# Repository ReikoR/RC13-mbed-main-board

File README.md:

RC13-mbed-main-board
====================

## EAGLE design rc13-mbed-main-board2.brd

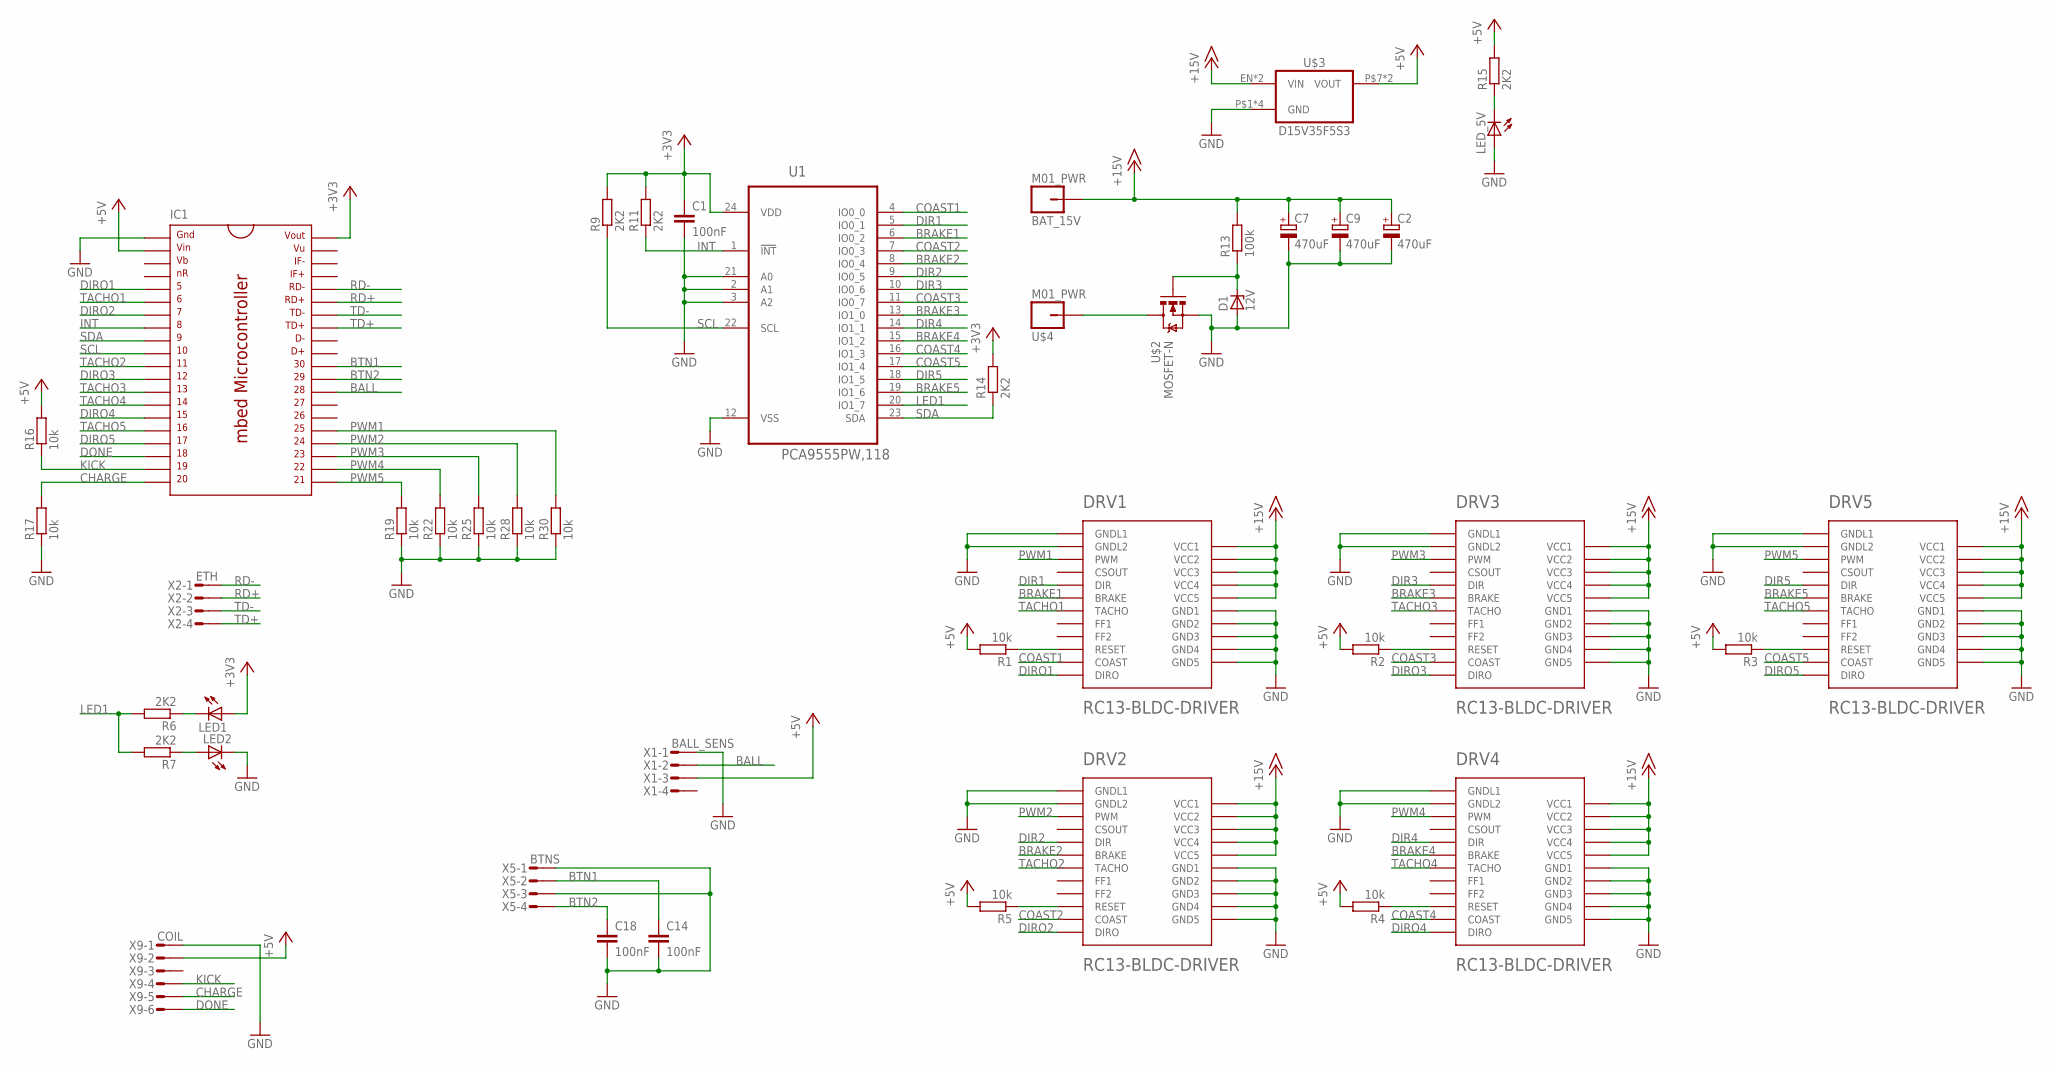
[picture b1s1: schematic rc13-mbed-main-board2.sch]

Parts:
BAT_15V: M01_PWR; PWR_HOLE
C1, C14, C18: 100nF; C0603K
C2, C7, C9: 470uF; E3,5-8
D1: 12V; SOD123
DRV1, DRV2, DRV3, DRV4, DRV5: RC13-BLDC-DRIVER
IC1: MBED_MICROCONTROLLER; DIL40_0.9
LED1, LED2: LEDCHIP-LED0603; CHIP-LED0603
LED_5V: LEDCHIP-LED0603; CHIP-LED0603
R1, R2, R3, R4, R5, R16, R17, R19, R22, R25, R28, R30: 10k; R0603
R6, R7, R9, R11, R14, R15: 2K2; R0603
R13: 100k; R0603
U1: PCA9555PW,118; SOP65P640X110-24N
U$2: MOSFET-N; TO127P600X120-5N
U$3: D15V35F5S3
U$4: M01_PWR; PWR_HOLE
X1: BALL_SENS; MICROMATCH-4
X2: ETH; MICROMATCH-4
X5: BTNS; MICROMATCH-4
X9: COIL; MICROMATCH-6

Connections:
+3V3: C1.1, IC1.40, LED1.A, R9.2, R11.2, R14.2, U1.24 (VDD)
+5V: IC1.2, R1.2, R2.2, R3.2, R4.2, R5.2, R15.2, R16.2, U$3.P$7 (VOUT), U$3.P$8 (VOUT), X1.3, X9.2
+15V: BAT_15V.P$1, C2.+, C7.+, C9.+, DRV1.PWR1 (VCC1), DRV1.PWR2 (VCC2), DRV1.PWR3 (VCC3), DRV1.PWR4 (VCC4), DRV1.PWR5 (VCC5), DRV2.PWR1 (VCC1), DRV2.PWR2 (VCC2), DRV2.PWR3 (VCC3), DRV2.PWR4 (VCC4), DRV2.PWR5 (VCC5), DRV3.PWR1 (VCC1), DRV3.PWR2 (VCC2), DRV3.PWR3 (VCC3), DRV3.PWR4 (VCC4), DRV3.PWR5 (VCC5), DRV4.PWR1 (VCC1), DRV4.PWR2 (VCC2), DRV4.PWR3 (VCC3), DRV4.PWR4 (VCC4), DRV4.PWR5 (VCC5), DRV5.PWR1 (VCC1), DRV5.PWR2 (VCC2), DRV5.PWR3 (VCC3), DRV5.PWR4 (VCC4), DRV5.PWR5 (VCC5), R13.2, U$3.EN (VIN), U$3.P$5 (VIN)
BALL: IC1.28, X1.2
BAT_GND: U$2.5 (D), U$4.P$1
BRAKE1: DRV1.LOGIC6 (BRAKE), U1.6 (IO0_2)
BRAKE2: DRV2.LOGIC6 (BRAKE), U1.8 (IO0_4)
BRAKE3: DRV3.LOGIC6 (BRAKE), U1.13 (IO1_0)
BRAKE4: DRV4.LOGIC6 (BRAKE), U1.15 (IO1_2)
BRAKE5: DRV5.LOGIC6 (BRAKE), U1.19 (IO1_6)
BTN1: C14.1, IC1.30, X5.2
BTN2: C18.1, IC1.29, X5.4
CHARGE: IC1.20, R17.2, X9.5
COAST1: DRV1.LOGIC11 (COAST), U1.4 (IO0_0)
COAST2: DRV2.LOGIC11 (COAST), U1.7 (IO0_3)
COAST3: DRV3.LOGIC11 (COAST), U1.11 (IO0_7)
COAST4: DRV4.LOGIC11 (COAST), U1.16 (IO1_3)
COAST5: DRV5.LOGIC11 (COAST), U1.17 (IO1_4)
DIR1: DRV1.LOGIC5 (DIR), U1.5 (IO0_1)
DIR2: DRV2.LOGIC5 (DIR), U1.9 (IO0_5)
DIR3: DRV3.LOGIC5 (DIR), U1.10 (IO0_6)
DIR4: DRV4.LOGIC5 (DIR), U1.14 (IO1_1)
DIR5: DRV5.LOGIC5 (DIR), U1.18 (IO1_5)
DIRO1: DRV1.LOGIC12 (DIRO), IC1.5
DIRO2: DRV2.LOGIC12 (DIRO), IC1.7
DIRO3: DRV3.LOGIC12 (DIRO), IC1.12
DIRO4: DRV4.LOGIC12 (DIRO), IC1.15
DIRO5: DRV5.LOGIC12 (DIRO), IC1.17
DONE: IC1.18, X9.6
GND: C1.2, C2.-, C7.-, C9.-, C14.2, C18.2, D1.A, DRV1.LOGIC1 (GNDL1), DRV1.LOGIC2 (GNDL2), DRV1.PWR6 (GND1), DRV1.PWR7 (GND2), DRV1.PWR8 (GND3), DRV1.PWR9 (GND4), DRV1.PWR10 (GND5), DRV2.LOGIC1 (GNDL1), DRV2.LOGIC2 (GNDL2), DRV2.PWR6 (GND1), DRV2.PWR7 (GND2), DRV2.PWR8 (GND3), DRV2.PWR9 (GND4), DRV2.PWR10 (GND5), DRV3.LOGIC1 (GNDL1), DRV3.LOGIC2 (GNDL2), DRV3.PWR6 (GND1), DRV3.PWR7 (GND2), DRV3.PWR8 (GND3), DRV3.PWR9 (GND4), DRV3.PWR10 (GND5), DRV4.LOGIC1 (GNDL1), DRV4.LOGIC2 (GNDL2), DRV4.PWR6 (GND1), DRV4.PWR7 (GND2), DRV4.PWR8 (GND3), DRV4.PWR9 (GND4), DRV4.PWR10 (GND5), DRV5.LOGIC1 (GNDL1), DRV5.LOGIC2 (GNDL2), DRV5.PWR6 (GND1), DRV5.PWR7 (GND2), DRV5.PWR8 (GND3), DRV5.PWR9 (GND4), DRV5.PWR10 (GND5), IC1.1, LED2.C, LED_5V.A, R17.1, R19.1, R22.1, R25.1, R28.1, R30.1, U1.2 (A1), U1.3 (A2), U1.12 (VSS), U1.21 (A0), U$2.1 (S), U$2.2 (S), U$2.3 (S), U$3.P$1 (GND), U$3.P$2 (GND), U$3.P$3 (GND), U$3.P$4 (GND), X1.1, X5.1, X5.3, X9.1
INT: IC1.8, R11.1, U1.1 (!INT)
KICK: IC1.19, R16.1, X9.4
LED1: R6.2, R7.2, U1.20 (IO1_7)
unnamed: DRV1.LOGIC10 (RESET), R1.1
unnamed: DRV2.LOGIC10 (RESET), R5.1
unnamed: DRV4.LOGIC10 (RESET), R4.1
unnamed: DRV5.LOGIC10 (RESET), R3.1
unnamed: DRV3.LOGIC10 (RESET), R2.1
unnamed: LED1.C, R6.1
unnamed: LED2.A, R7.1
unnamed: LED_5V.C, R15.1
unnamed: D1.C, R13.1, U$2.4 (G)
PWM1: DRV1.LOGIC3 (PWM), IC1.25, R30.2
PWM2: DRV2.LOGIC3 (PWM), IC1.24, R28.2
PWM3: DRV3.LOGIC3 (PWM), IC1.23, R25.2
PWM4: DRV4.LOGIC3 (PWM), IC1.22, R22.2
PWM5: DRV5.LOGIC3 (PWM), IC1.21, R19.2
RD+: IC1.35, X2.2
RD-: IC1.36, X2.1
SCL: IC1.10, R9.1, U1.22 (SCL)
SDA: IC1.9, R14.1, U1.23 (SDA)
TACHO1: DRV1.LOGIC7 (TACHO), IC1.6
TACHO2: DRV2.LOGIC7 (TACHO), IC1.11
TACHO3: DRV3.LOGIC7 (TACHO), IC1.13
TACHO4: DRV4.LOGIC7 (TACHO), IC1.14
TACHO5: DRV5.LOGIC7 (TACHO), IC1.16
TD+: IC1.33, X2.4
TD-: IC1.34, X2.3

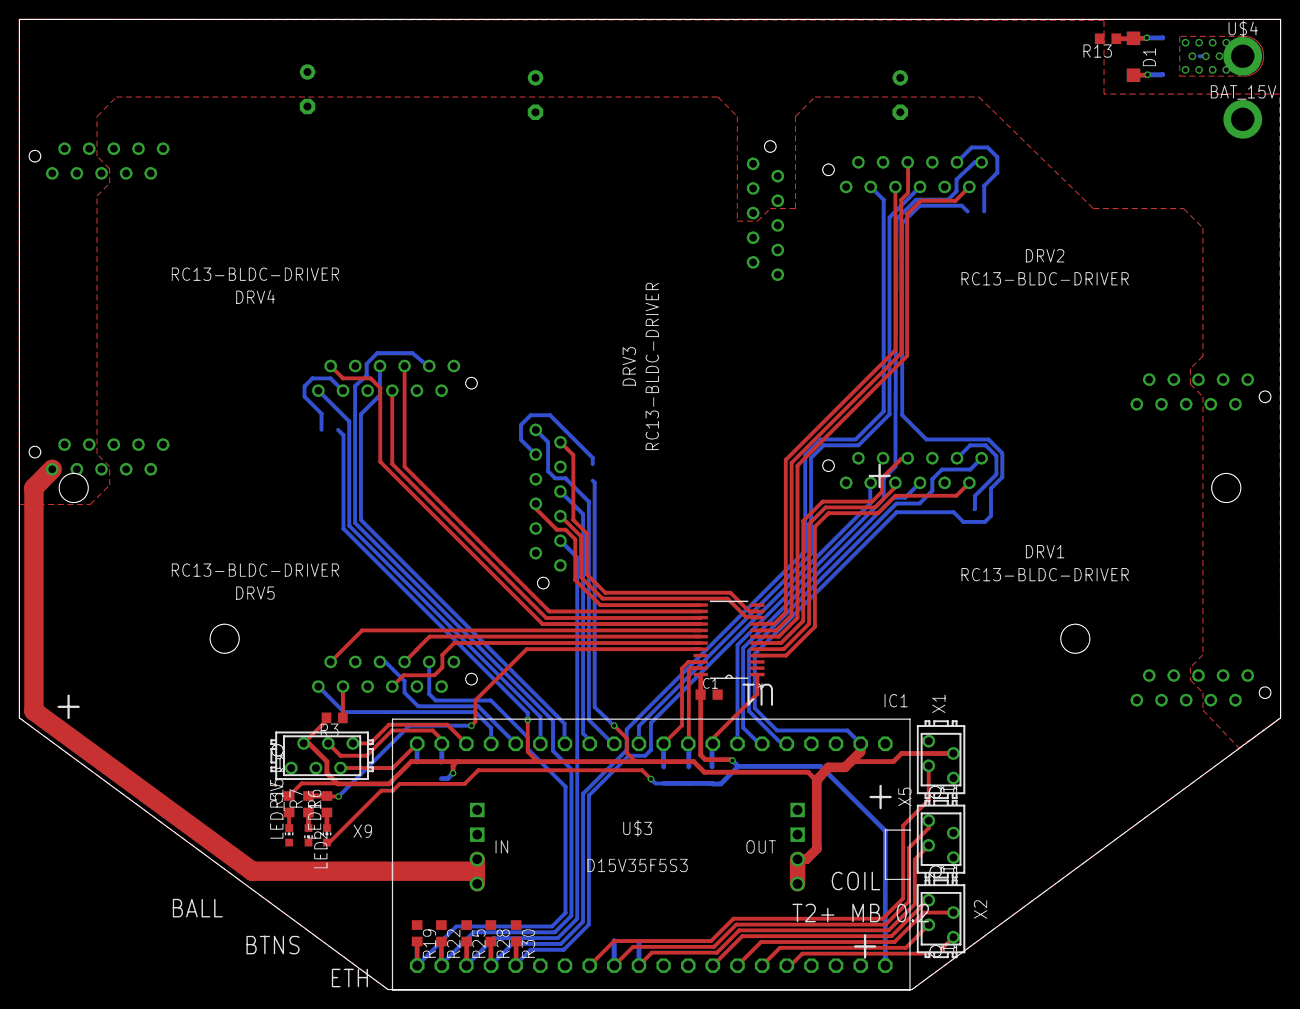
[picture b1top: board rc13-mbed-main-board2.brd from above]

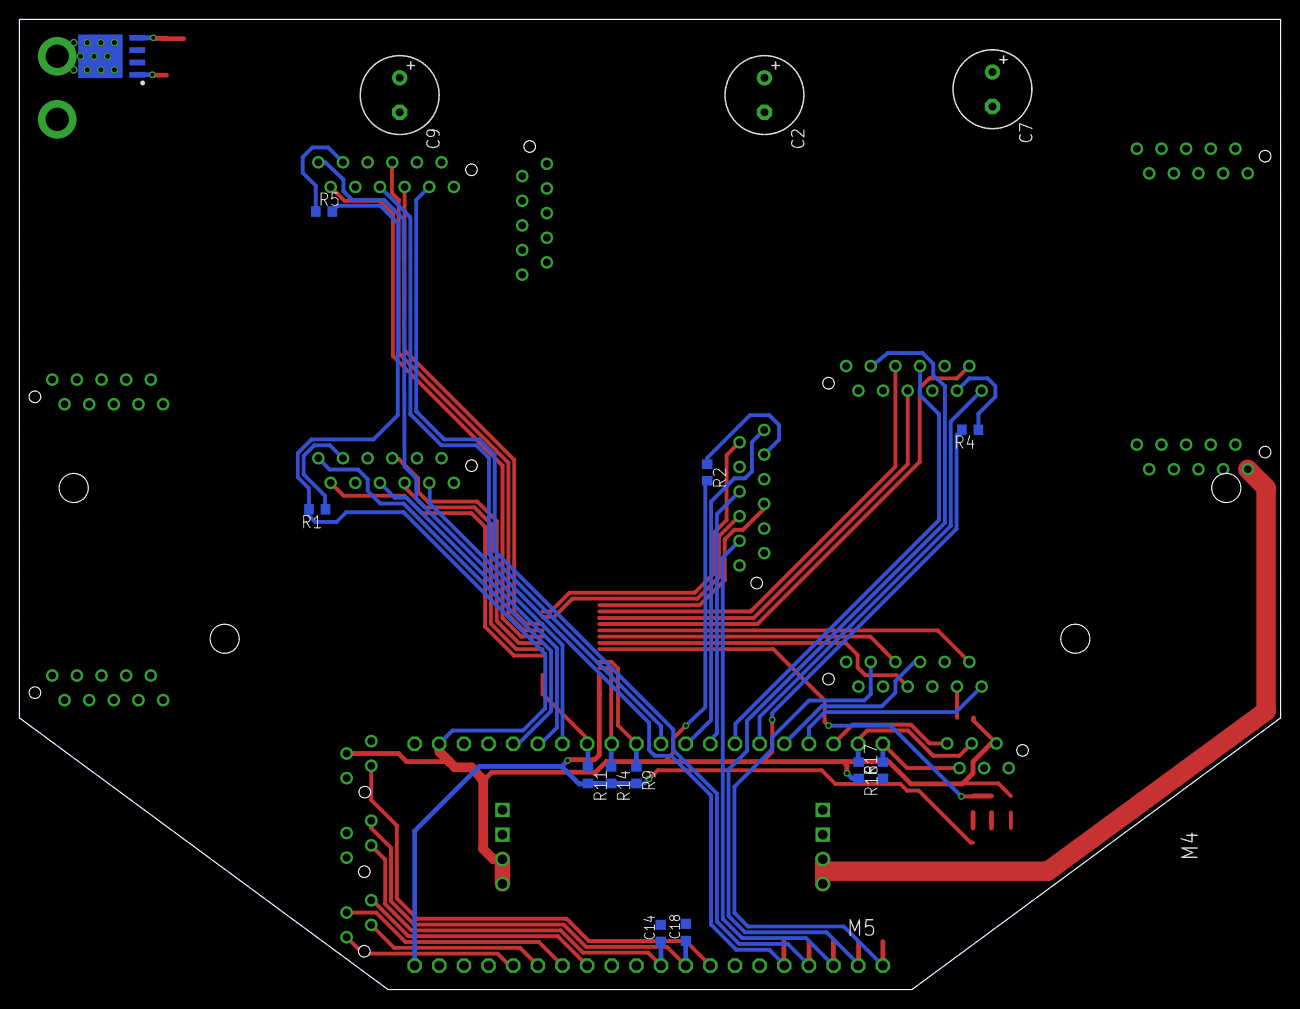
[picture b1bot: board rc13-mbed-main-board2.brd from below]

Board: 2 copper layers, 130.0 x 100.0 mm, 44 parts (15 on the bottom side), 58 nets.

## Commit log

2013-10-01 Started designing mbed controlled main board
2013-10-02 Routed some board
2013-10-05 Moved bottom drivers together to make room on the sides
2013-10-06 Added mounting slots on the sides
2013-10-07 Some routing changes
2013-10-19 Fixed micromatch pin layout
2013-10-21 Created better board layout
2013-10-22 Improved routing
2013-10-22 Few small changes

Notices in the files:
parts and their libraries:
nxp_sot669: Licensing: CC v3.0 Share-Alike You are welcome to use this library for commercial purposes.
